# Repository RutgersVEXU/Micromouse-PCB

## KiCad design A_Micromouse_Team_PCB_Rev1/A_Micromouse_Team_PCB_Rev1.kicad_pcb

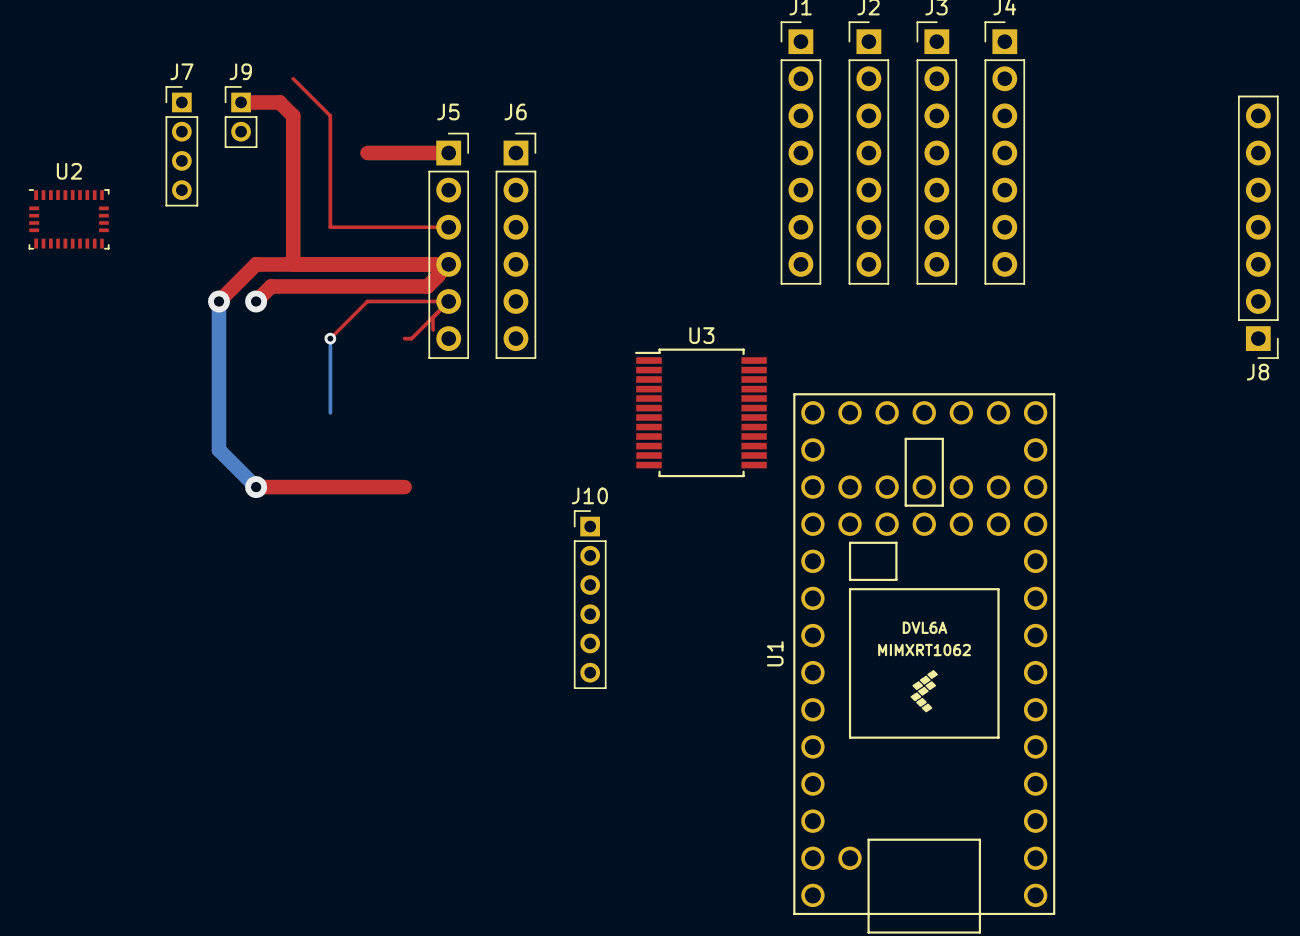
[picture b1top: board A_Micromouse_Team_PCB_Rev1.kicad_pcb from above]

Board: 2 copper layers, 13 parts (0 on the bottom side), 30 nets.

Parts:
J1, J2, J3, J4, J8: Conn_01x07_Pin; PinHeader_1x07_P2.54mm_Vertical
J5, J6: Conn_01x06_Pin; PinSocket_1x06_P2.54mm_Vertical
J7: Conn_01x04_Socket; PinHeader_1x04_P2.00mm_Vertical
J9: Conn_01x02_Socket; PinHeader_1x02_P2.00mm_Vertical
J10: Conn_01x06; PinHeader_1x06_P2.00mm_Vertical
U1: Teensy4.0; Teensy40
U2: BNO055; LGA-28_5.2x3.8mm_P0.5mm
U3: TB6612FNG; SSOP-24_5.3x8.2mm_P0.65mm

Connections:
+5V: J1.2, J2.2, J3.2, J4.2, J5.4, J6.4, J7.3, J8.2, J9.1, J10.4, J10.5, U3.20 (VCC)
+12V: J10.1, U3.24 (VM1)
GND: J5.1, J6.1, J7.1, J7.4, J9.2, J10.2, J10.3, U3.18 (GND)
GND1: J1.3, J2.3, J3.3, J4.3, J8.3
unnamed: J1.6, U1.7 (5_IN2)
unnamed: J2.6, U1.6 (4_BCLK2)
unnamed: J3.6, U1.5 (3_LRCLK2)
unnamed: J4.6, U1.4 (2_OUT2)
unnamed: J5.2, U1.13 (11_MOSI_CTX1)
unnamed: J5.3, U1.14 (12_MISO_MQSL)
unnamed: J5.5, U3.7 (BO2), U3.8 (BO2)
unnamed: J5.6, U3.11 (BO1), U3.12 (BO1)
unnamed: J6.2, U1.11 (9_OUT1C)
unnamed: J6.3, U1.12 (10_CS_MQSR)
unnamed: J6.5, U3.5 (AO2), U3.6 (AO2)
unnamed: J6.6, U3.1 (AO1), U3.2 (AO1)
unnamed: J7.2, U1.22 (15_A1_RX3_SPDIF_IN)
unnamed: J8.6, U1.8 (6_OUT1D)
unnamed: U1.9 (7_RX2_OUT1A), U3.15 (PWMB)
unnamed: U1.10 (8_TX2_IN1), U3.23 (PWMA)
unnamed: U1.20 (13_SCK_CRX1_LED), U3.19 (STBY)
unnamed: U1.23 (16_A2_RX4_SCL1), U3.21 (AIN1)
unnamed: U1.24 (17_A3_TX4_SDA1), U3.22 (AIN2)
unnamed: U1.29 (22_A8_CTX1), U3.17 (BIN1)
unnamed: U1.30 (23_A9_CRX1_MCLK1), U3.16 (BIN2)
unnamed: U2.15 (GNDIO), U2.16 (GNDIO), U2.25 (GNDIO)
unnamed: U3.3 (PGND1), U3.4 (PGND1)
unnamed: U3.9 (PGND2), U3.10 (PGND2)
SCL: J1.5, J2.5, J3.5, J4.5, J8.5, U1.26 (19_A5_SCL0)
SDA: J1.4, J2.4, J3.4, J4.4, J8.4, U1.25 (18_A4_SDA0)

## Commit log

2024-02-01 changed Net Classes
